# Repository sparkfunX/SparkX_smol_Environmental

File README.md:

# SparkX smôl Environmental Peripheral Board

[*SparkX smôl Environmental Peripheral Board (SPX-18976)*](https://www.sparkfun.com/products/18976)

An environmental board for smôl:
- **BME280** - Pressure, Humidity and Temperature sensor
- **SGP40** - VOC air quality sensor
- **VEML7700** - ambient light sensor (top view)

## Repository Contents

- [**/Hardware**](./Hardware) - Eagle PCB, SCH and LBR design files
- [**LICENSE.md**](./LICENSE.md) - contains the licence information

## Product Versions

- [SPX-18976](https://www.sparkfun.com/products/18976) - Original SparkX Release.

## License Information

This product is _**open source**_!

Please review the LICENSE.md file for license information.

If you have any questions or concerns on licensing, please contact technical support on our [SparkFun forums](https://forum.sparkfun.com/viewforum.php?f=123).

Distributed as-is; no warranty is given.

- Your friends at SparkFun.

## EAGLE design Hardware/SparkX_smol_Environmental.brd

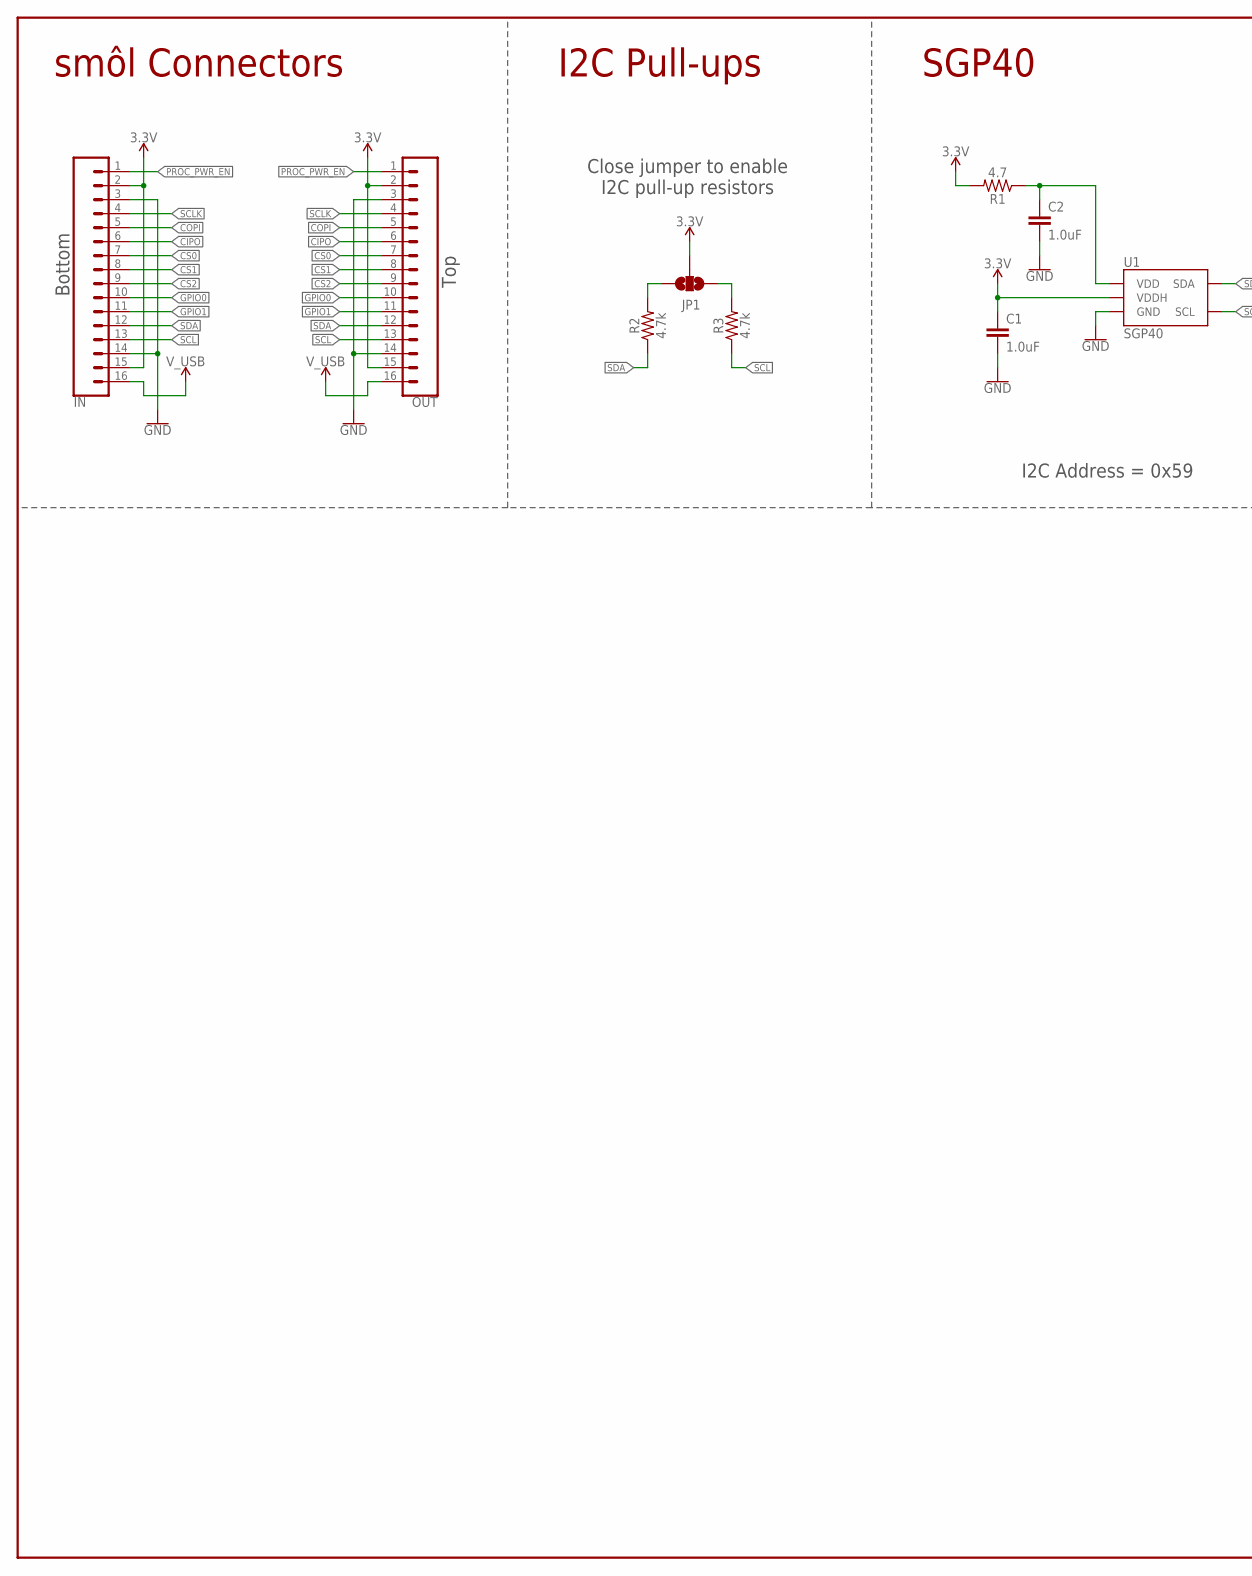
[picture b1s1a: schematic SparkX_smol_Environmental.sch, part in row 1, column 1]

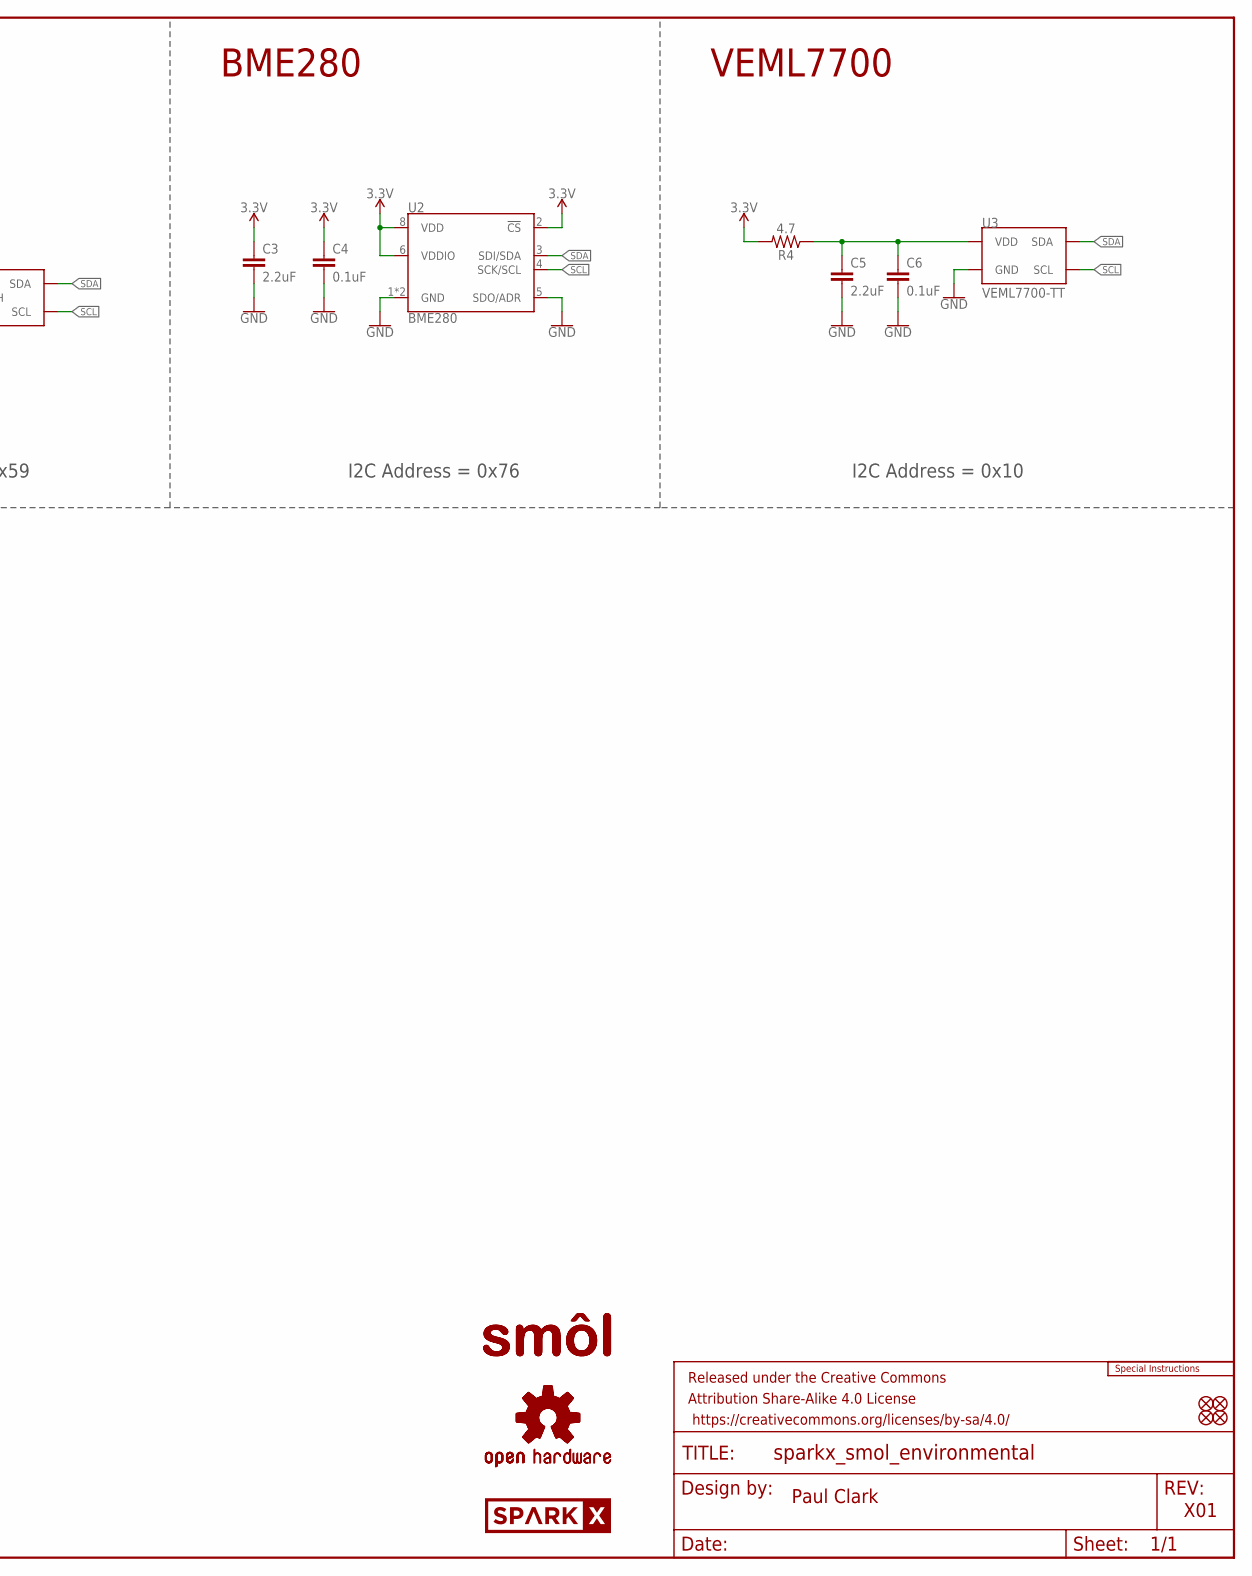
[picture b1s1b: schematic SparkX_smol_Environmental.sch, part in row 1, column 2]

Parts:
C1, C2: 1.0uF; 0402-TIGHT
C3, C5: 2.2uF; 0402-TIGHT
C4, C6: 0.1uF; 0402-TIGHT
FD1, FD2, FD3, FD4: FIDUCIALUFIDUCIAL; FIDUCIAL-MICRO
FRAME1: FRAME-LEDGER; CREATIVE_COMMONS
IN: CONN_16FPC_16_0.5MM; FPC_16_0.5MM
JP1: JUMPER-SMT_3_NO_SILK; SMT-JUMPER_3_NO_SILK
LOGO1: SPECIAL_INSTRUCTIONS-ORDERING; ORDERING_INSTRUCTIONS
LOGO2, LOGO3: OSHW-LOGOMINI; OSHW-LOGO-MINI
OUT: CONN_16FPC_16_0.5MM; FPC_16_0.5MM
R1, R4: 4.7; 0402-TIGHT
R2, R3: 4.7k; 0402-TIGHT
U1: SGP40
U2: BME280; LGA-8-2.5X2.5
U3: VEML7700-TT; VEML7700_TT
U$1: SPARKX-LOGO3; SPARKX-SMALL
U$3, U$9: SMOL_LOGOSMALL; SMOL_SMALL

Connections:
3.3V: C1.1, C3.1, C4.1, IN.2, IN.15, JP1.2, OUT.2, OUT.15, R1.2, R4.2, U1.5 (VDDH), U2.2 (!CS), U2.6 (VDDIO), U2.8 (VDD)
CIPO: IN.6, OUT.6
COPI: IN.5, OUT.5
CS0: IN.7, OUT.7
CS1: IN.8, OUT.8
CS2: IN.9, OUT.9
GND: C1.2, C2.2, C3.2, C4.2, C5.2, C6.2, IN.3, IN.14, OUT.3, OUT.14, U1.2 (GND), U1.4 (GND), U1.DIEPAD (GND), U2.1 (GND), U2.5 (SDO/ADR), U2.7 (GND), U3.3 (GND)
GPIO0: IN.10, OUT.10
GPIO1: IN.11, OUT.11
unnamed: C2.1, R1.1, U1.1 (VDD)
unnamed: JP1.3, R2.2
unnamed: JP1.1, R3.2
unnamed: C5.1, C6.1, R4.1, U3.2 (VDD)
PROC_PWR_EN: IN.1, OUT.1
SCL: IN.13, OUT.13, R3.1, U1.6 (SCL), U2.4 (SCK/SCL), U3.1 (SCL)
SCLK: IN.4, OUT.4
SDA: IN.12, OUT.12, R2.1, U1.3 (SDA), U2.3 (SDI/SDA), U3.4 (SDA)
V_USB: IN.16, OUT.16

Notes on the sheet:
Paul Clark
X01
smôl Connectors
Top
Bottom
SGP40
BME280
VEML7700
I2C Address = 0x10
I2C Address = 0x59
Close jumper to enable I2C pull-up resistors
I2C Address = 0x76
I2C Pull-ups

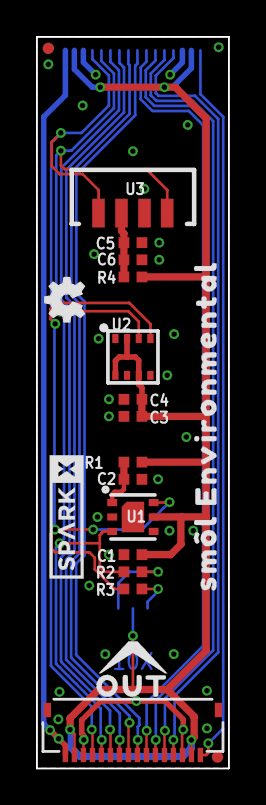
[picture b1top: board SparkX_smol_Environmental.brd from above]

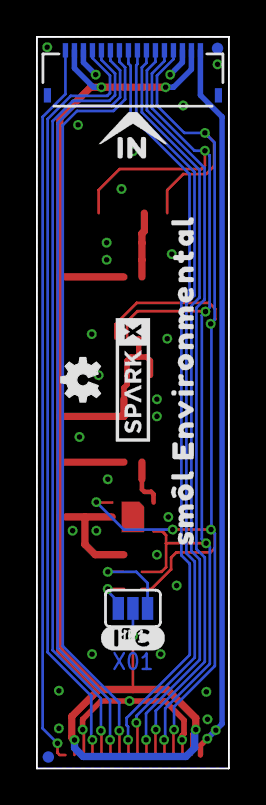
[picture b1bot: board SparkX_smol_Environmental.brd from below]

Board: 2 copper layers, 10.7 x 40.6 mm, 33 parts (10 on the bottom side), 18 nets.

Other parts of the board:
U$2, U$4: SM�L_ENVIRONMENTAL0
U$5: #I�C#0
U$8: IN0
U$17: OUT0
U$20: SPARKX-LOGO3; SPARKX-SMALL

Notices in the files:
parts and their libraries:
SparkFun-Aesthetics: Licensing: Creative Commons ShareAlike 4.0 International - https://creativecommons.org/licenses/by-sa/4.0
SparkFun-Aesthetics: Released under the Creative Commons Attribution Share-Alike 4.0 License
SparkFun-Aesthetics: https://creativecommons.org/licenses/by-sa/4.0
